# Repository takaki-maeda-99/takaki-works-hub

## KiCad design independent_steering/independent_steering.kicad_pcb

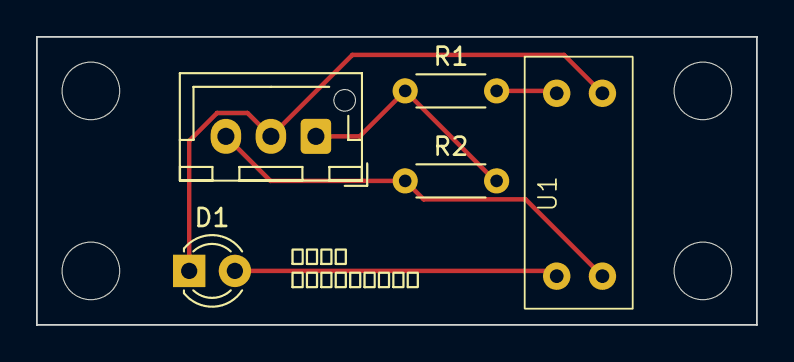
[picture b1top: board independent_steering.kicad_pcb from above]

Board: 2 copper layers, 40.0 x 16.0 mm, 5 parts (0 on the bottom side), 5 nets.

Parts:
D1: LED; LED_D3.0mm
J1: Conn_01x03_Socket; JST_XH_B3B-XH-AM_1x03_P2.50mm_Vertical
R1: 330; R_Axial_DIN0204_L3.6mm_D1.6mm_P5.08mm_Horizontal
R2: 10k; R_Axial_DIN0204_L3.6mm_D1.6mm_P5.08mm_Horizontal
U1: TLP806

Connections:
+5V: J1.1, R1.1, R2.2
GND: D1.1 (K), J1.2, U1.2 (K)
unnamed: D1.2 (A), U1.4 (E)
unnamed: R1.2, U1.1 (A)
OUT: J1.3, R2.1, U1.3 (C)

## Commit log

2025-06-10 rename
2025-07-06 Refactor CAN receive callbacks
2025-07-07 Revert "Unify CAN receive logic"
2025-08-14 0814
2025-08-14 homing
2025-08-29 windows11を恐れて
